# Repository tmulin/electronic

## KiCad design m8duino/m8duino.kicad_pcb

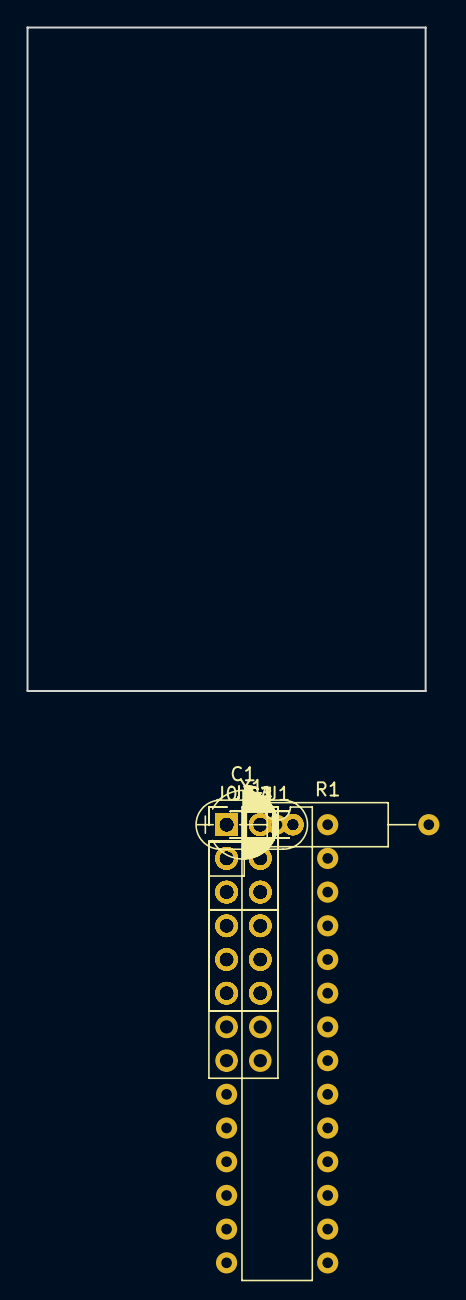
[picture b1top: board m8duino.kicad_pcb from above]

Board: 2 copper layers, 30.0 x 50.0 mm, 13 parts (0 on the bottom side), 8 nets, no tracks yet.

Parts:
C1: 10uF; CP_Radial_D5.0mm_P2.50mm
C2: 10pF; C_Disc_D4.3mm_W1.9mm_P5.00mm
C3, C4: 22pF; C_Disc_D4.3mm_W1.9mm_P5.00mm
J0: Conn_01x02; Pin_Header_Straight_1x02_Pitch2.54mm
J1: ISP; Pin_Header_Straight_2x03_Pitch2.54mm
J2: ANA; Pin_Header_Straight_2x03_Pitch2.54mm
J3: D8-13; Pin_Header_Straight_2x06_Pitch2.54mm
J4: A0-5; Pin_Header_Straight_2x06_Pitch2.54mm
J5: D0-7; Pin_Header_Straight_2x08_Pitch2.54mm
R1: 10k; R_Axial_DIN0309_L9.0mm_D3.2mm_P15.24mm_Horizontal
U1: ATMEGA8L-8PU; DIP-28_W7.62mm
Y1: 8M; Crystal_HC52-U_Vertical

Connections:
+5V: C1.1, C2.1, J0.1, J1.2, R1.1, U1.7
/D11: J1.4, U1.17
/D12: J1.1, U1.18
/D13: J1.3, U1.19
/RESET: J1.5, R1.2, U1.1
GND: C1.2, C2.2, C3.2, C4.2, J0.2, J1.6, U1.8
unnamed: C3.1, U1.9, Y1.2
unnamed: C4.1, U1.10, Y1.1

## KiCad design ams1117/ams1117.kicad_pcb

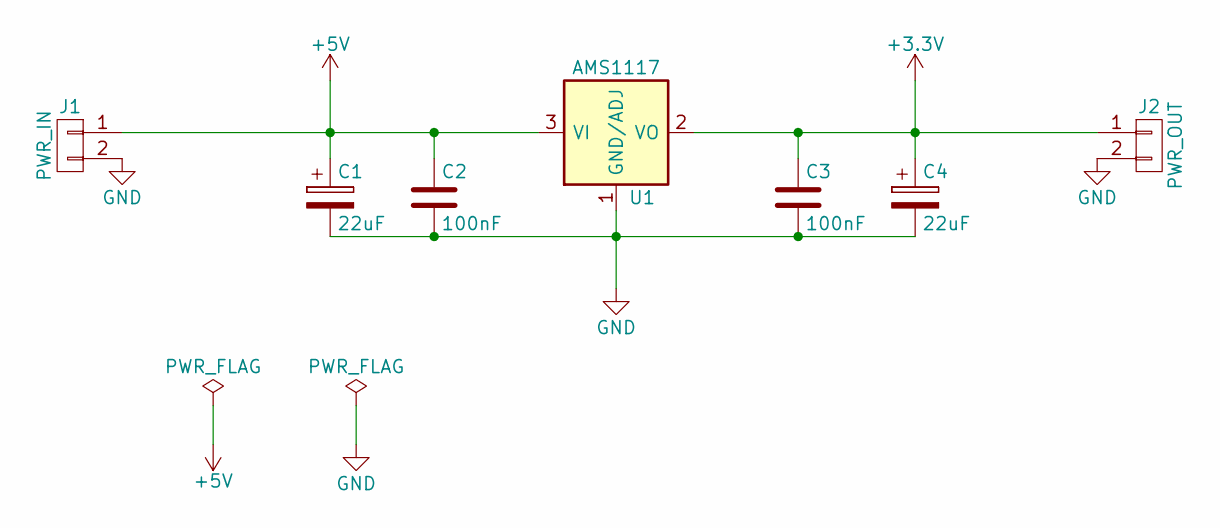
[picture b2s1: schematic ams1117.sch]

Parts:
C1, C4: 22uF; CP_Elec_5x5.3
C2, C3: 100nF; C_1206
J1: PWR_IN; Pin_Header_Straight_1x02_Pitch2.54mm
J2: PWR_OUT; Pin_Header_Straight_1x02_Pitch2.54mm
U1: AMS1117; SOT-223

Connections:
+3V3: C3.1, C4.1, J2.1, U1.2 (VO)
+5V: C1.1, C2.1, J1.1, U1.3 (VI)
GND: C1.2, C2.2, C3.2, C4.2, J1.2, J2.2, U1.1 (GND/ADJ)

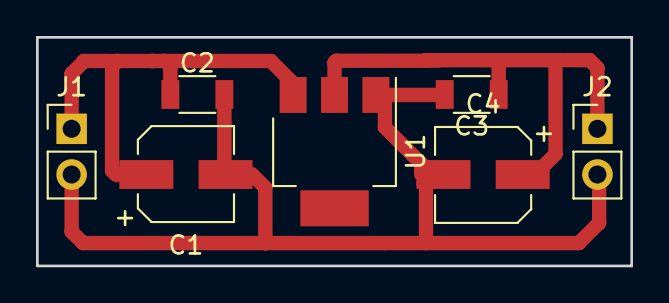
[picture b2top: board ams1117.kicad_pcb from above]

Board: 2 copper layers, 33.0 x 12.7 mm, 7 parts (0 on the bottom side), 3 nets.

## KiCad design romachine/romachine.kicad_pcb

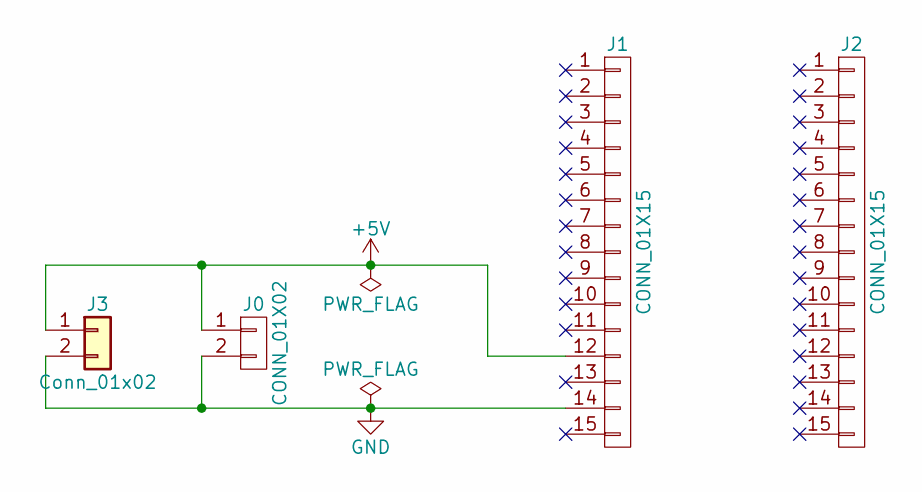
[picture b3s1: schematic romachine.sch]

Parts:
J0: CONN_01X02; Socket_Strip_Straight_1x02_Pitch2.54mm
J1, J2: CONN_01X15; Socket_Strip_Straight_1x15_Pitch2.54mm
J3: Conn_01x02; Pin_Header_Straight_1x02_Pitch2.54mm

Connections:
+5V: J0.1, J1.12, J3.1
GND: J0.2, J1.14, J3.2

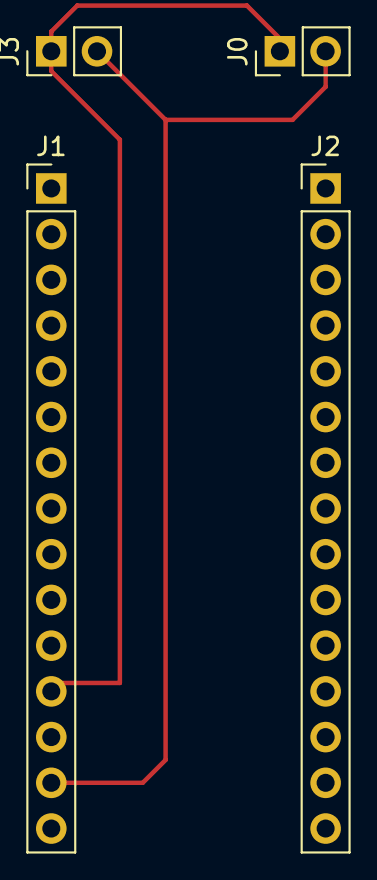
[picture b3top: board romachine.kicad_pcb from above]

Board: 2 copper layers, 4 parts (0 on the bottom side), 2 nets.

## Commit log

2017-11-10 提交测试 KiCad 项目及个人元件库
2017-11-10 完成AMS1117降压模块PCB绘制
2017-11-16 增加基于ATMega8L-8PU的 Arduino 系统板
2017-11-17 完成测试板绘制;增加自动布线测试;
2017-11-18 调整为 Arduino 系统开发板
